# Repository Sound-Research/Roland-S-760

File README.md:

# Roland S-760

## Overview
Documentation for the Roland S-760 sampler.

## Specifications
- Type: Sampler
- Manufacturer: Roland

## Mouse

The S-760 uses a DB-9 mouse port with the **MSX mouse protocol** (nibble-clock based, originally MITSUMI).
The original Roland mouse is the MU-1, which is a rebranded MITSUMI MSX mouse.

**Important:** The MSX DB-9 pinout has **pin 5 = +5V** and **pin 9 = GND**, which is **reversed** compared to Atari/Amiga DB-9 (pin 7 = +5V, pin 8 = GND).
Atari, Amiga, and Commodore mice are **not compatible** — they use different protocols and reversed power pins.

### Compatible adapters

#### MSX PS/2 mouse interface (recommended)

- **Source**: [Gotek Retro](https://www.gotek-retro.eu/msx-ps2-mouse-interface/) or [Tindie (Denjhang)](https://www.tindie.com/products/denjhang/msx-ps2-mouse-converter/)
- **Description**: ATtiny2313-based PS/2 to MSX mouse protocol converter
- **Status**: Confirmed working with S-760
- **Note**: Pressing both mouse buttons simultaneously toggles between mouse and joystick emulation modes, so simultaneous two-button operations don't work
- **Requires**: A native PS/2 mouse, or a USB mouse with genuine PS/2 compatibility mode (not all passive USB-to-PS/2 adapters work)

#### USB-to-MSX mouse adapter

- **Source**: Occasionally available on eBay (search "USB to MSX Mouse Adapter Towns Roland")
- **Description**: Direct USB to MSX mouse protocol converter
- **Status**: Confirmed working with S-760 by users
- **Note**: Small-batch/hobbyist product, stock varies

#### Original MSX mice

Any genuine MSX mouse works (Roland MU-1, Philips MSX mouse, etc.).
Increasingly rare and expensive.

### DIY USB-to-MSX mouse adapter

Two open-source projects exist using a **Raspberry Pi Pico** (RP2040):

#### MsxUsbMouseConverter (recommended)

- **Source**: [Retro-Do-MSX/MsxUsbMouseConverter](https://github.com/Retro-Do-MSX/MsxUsbMouseConverter)
- **Description**: USB mouse to MSX mouse converter using RP2040
- **Hardware**: Raspberry Pi Pico + USB-A female connector + 2x 22-ohm resistors + DB9 cable
- **Advantage**: Operates exclusively in MSX mouse mode (no joystick toggle), so both buttons work simultaneously — unlike the PS/2 adapter above
- **Includes**: 3D-printable case files

#### unz-hid-pico

- **Source**: [hsshss/unz-hid-pico](https://github.com/hsshss/unz-hid-pico)
- **Description**: USB mouse/gamepad to FM TOWNS and MSX protocol converter
- **Hardware**: Raspberry Pi Pico + OTG adapter + DB9 cable + 3.3V-to-5V level shifter
- **Schematic**: [OSHWLab](https://oshwlab.com/hsshss/unz-hid-pico)

#### Why not other microcontrollers?

- **ESP32 (original)**: No native USB host — software USB host exists but is unreliable
- **ESP32-S2/S3**: Has USB host but no existing MSX mouse project — would need custom firmware from scratch
- **Arduino Duemilanove**: No USB host — requires a USB Host Shield (MAX3421E) add-on board
- **Raspberry Pi Zero 2 W**: Linux is not real-time enough for the MSX protocol timing (0.18 ms clock response), and GPIO is 3.3V (MSX expects 5V)

### mouSTer USB mouse adapter (not compatible)

- **Source**: [C64 OS Store](https://c64os.com/store/)
- **Status**: **Not compatible** — does not support MSX protocol (only Atari ST, Amiga, and C64 modes)
- **Note**: Previously recommended by Claude in error, purchased based on that recommendation, and confirmed not to work with the S-760. The mouSTer lacks MSX protocol support entirely.

## Video Output

The S-760 (with OP-760-1 expansion) has a digital RGB video output via an 8-pin DIN connector.

### OP-760-1 video signal specifications

- **Signal type**: TTL digital RGB (RGBS — 1 bit per channel, 8 colours max)
- **Resolution**: 640x200 (CGA-class)
- **Horizontal sync**: ~15.7 kHz
- **Vertical sync**: ~60 Hz
- **Sync type**: Separate H-Sync and V-Sync
- **Connector**: 8-pin DIN (EIAJ)

#### DIN-8 pinout

| Pin | Signal |
| --- | --- |
| 1 | +5V (do not connect to RGBtoHDMI) |
| 2 | GND |
| 3 | No connection |
| 4 | H-Sync |
| 5 | V-Sync |
| 6 | Red |
| 7 | Green |
| 8 | Blue |

**Note:** Some sources (e.g. S-550 manual) list a different pin assignment.
Verify against your hardware or use a known-good pre-made cable.

#### References

- [llamamusic.com DIY page](https://llamamusic.com/s50s550/DIY_page.html) — S-50/S-550/S-760 video output details and DIN-8 pinout
- [llamamusic.com RGB-25N cable DIY](https://llamamusic.com/s50s550/Roland_RGB-25N_Monitor_Cable_DIY.html) — cable wiring guide
- [Jim Atwood — S-760 with OP-760-1](https://jimatwood.wordpress.com/2012/02/01/roland-s-760-sampler-with-op-760-1-video-output-and-mu-1-mouse/) — working setup photos
- [s760.free.fr monitors page](http://s760.free.fr/monitor.htm) — compatible monitor list

### RGBtoHDMI

- **Source**: [hoglet67/RGBtoHDMI](https://github.com/hoglet67/RGBtoHDMI)
- **Description**: Converts retro computer RGB/YUV video signals to HDMI
- **Hardware**: Raspberry Pi Zero + custom hat with CPLD
- **License**: GPL-3.0

#### Profile selection

Use **6-12_BIT_RGB > IBM PC Compatible > CGA**.
The S-760's video output matches CGA timing and signal characteristics (TTL RGB, 15.7 kHz, 200 lines, separate H/V sync).

#### Fullscreen output

By default RGBtoHDMI may show the image in a small window with black borders.
To get fullscreen output, use the on-screen menu (active button on the hat):

1. Press **Menu** button on the RGBtoHDMI hat
2. Navigate to **Scaling** settings
3. Set scaling to **Fill** or **Integer** (integer gives pixel-perfect scaling without stretching)
4. Adjust **overscan** values if there are still black borders

You can also try different **Resolution** options in the menu — some HDMI displays respond better to specific output resolutions (e.g. 1080p vs 720p).

#### Raspberry Pi setup

The RGBtoHDMI runs bare-metal firmware on a Raspberry Pi Zero (no OS needed).

1. **Download** the latest release zip from [hoglet67/RGBtoHDMI releases](https://github.com/hoglet67/RGBtoHDMI/releases)
2. **Format** a micro SD card as FAT32
3. **Extract** the zip to the root of the SD card (files should be in the root directory, not in a subfolder)
4. **Safely eject** the SD card from the PC
5. **Insert** the SD card into the Pi Zero

- **Recommended Pi**: Raspberry Pi Zero (non-W) — the WiFi radio on the W models can cause visual artifacts
- **If using a Pi Zero W**: disable radios by adding `dtoverlay=disable-wifi` and `dtoverlay=disable-bt` to `config.txt` on the SD card
- **Avoid Pi Zero 2 W**: different GPIO timing causes compatibility issues
- **Upgrading**: wipe the SD card first, do not overwrite an existing install — old saved profiles are not guaranteed to be compatible

## SCSI Storage

The S-760 uses SCSI for external storage. A ZuluSCSI Pico Slim replaces physical SCSI drives with SD card-based disk images.

### ZuluSCSI Pico Slim

- **Source**: [SamplerZone](https://samplerzone.com/products/zuluscsi-pico-slim)
- **Description**: Ultra-compact SCSI SD card emulator with DB25 connector
- **Hardware**: Raspberry Pi Pico W in a mini plug-in case
- **Included**: Pre-configured 64GB SD card
- **Features**:
  - Supports up to 7 SCSI IDs (multiple drives simultaneously)
  - Plug-and-play via DB25 SCSI port
  - Standard SD card with disk image files
  - Compatible with Roland, Akai, Ensoniq, Emu, Kurzweil, Korg, Yamaha samplers

## Sound Loading

Chicken Systems Translator is used to convert and load sounds onto the ZuluSCSI disk images for use on the S-760.

### Chicken Systems Translator 7

- **Source**: [Chicken Systems](https://www.chickensys.com/products2/translator/index.html)
- **Description**: Professional sample library conversion software
- **Platforms**: Mac OS X, Windows
- **Features**:
  - Converts between 50+ sampler and DAW formats including Roland, Akai, Emu, Kontakt, EXS24, SFZ, GigaStudio
  - Translates wavedata, keymaps, and effects parameters
  - Built-in Instrument Player for auditioning sounds before conversion
  - Reference Manager for repairing broken sample links
  - AutoSampler for recording internal and external equipment

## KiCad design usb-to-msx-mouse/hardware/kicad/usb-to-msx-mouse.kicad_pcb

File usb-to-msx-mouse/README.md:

# USB-to-MSX mouse adapter for Roland S-760

Open-source hardware adapter that lets you use a standard USB mouse (like the Logitech Trackman Marble) with the Roland S-760 sampler.

The S-760 uses the MSX mouse protocol on a DB-9 joystick port.
Original Roland MU-1 mice are rare and expensive.
This adapter is a custom PCB with an RP2040 microcontroller that translates USB HID mouse reports into MSX nibble protocol in real time.

## Features

- **Plug and forget** — no drivers, no configuration
- **USB-A input** — works with any standard USB mouse (boot protocol)
- **DB-9 output** — connects to the S-760's mouse port via standard serial cable
- **Custom PCB** — RP2040 directly on board (not a Pico module), ~20×40mm
- **JLCPCB-ready** — full production files included (Gerbers, BOM, CPL)
- **Under $16 NZD per unit** (in batches of 5)

## How it works

```
USB Mouse → [USB-A] → RP2040 (TinyUSB host) → 74HCT245 → [DB-9] → S-760
              ↑                                    ↑
           USB HID                           3.3V → 5V
         boot protocol                     level shifting
```

1. The RP2040 runs TinyUSB in USB host mode, receiving HID boot-protocol mouse reports
1. Mouse X/Y deltas accumulate between read cycles, scaled from USB DPI to MSX ~200 DPI
1. When the S-760 toggles the strobe line (DB-9 pin 8), a GPIO interrupt handler serves 4 nibbles of position data
1. Button state is output continuously on DB-9 pins 6 and 7
1. A 74HCT245 level shifter converts all outputs from 3.3V to 5V MSX levels

## Project structure

```
usb-to-msx-mouse/
├── firmware/           Pico SDK C project (TinyUSB host + MSX protocol)
│   ├── CMakeLists.txt
│   ├── src/            main.c, hid_app.c, mouse.c, config.h
│   └── include/        tusb_config.h
├── hardware/
│   ├── kicad/          KiCad 8 schematic and PCB layout
│   ├── bom.csv         Bill of materials with JLCPCB part numbers
│   ├── gerbers/        Production Gerber files
│   └── jlcpcb/         JLCPCB assembly files (BOM + CPL)
├── case/               3D printable snap-fit enclosure (STEP + STL)
├── docs/
│   ├── pinout.md       GPIO to DB-9 pin mapping
│   └── build-guide.md  Order, flash, assemble, test
├── LICENSE             MIT
└── README.md
```

## Quick start

### Build firmware

```bash
export PICO_SDK_PATH=/path/to/pico-sdk
cd firmware
mkdir build && cd build
cmake ..
make -j$(nproc)
```

### Flash

1. Hold BOOTSEL button on the PCB
1. Connect USB-A to USB-A cable between computer and adapter
1. Release BOOTSEL — adapter appears as `RPI-RP2` drive
1. Copy `build/usb-to-msx-mouse.uf2` to the drive

### Connect

1. DB-9 cable from adapter to S-760 mouse port
1. Plug USB mouse into adapter's USB-A port
1. Green LED lights up when mouse is recognized
1. Power on S-760 — cursor should work

See [docs/build-guide.md](docs/build-guide.md) for full step-by-step instructions.

## Configuration

Edit `firmware/src/config.h` to adjust:

- **`MOUSE_DPI`** — match your mouse's native DPI (300 for Trackman Marble, 800 for typical optical)
- **`MOUSE_DATA_REVERSE`** — set to 1 if data lines are wired in reverse order
- **Pin assignments** — if modifying the PCB layout

## Hardware specifications

- **MCU**: RP2040 (QFN-56, dual-core Cortex-M0+, 133 MHz)
- **Flash**: W25Q16JVSNIQ (2MB QSPI)
- **Level shifter**: 74HCT245 (SOIC-20)
- **Power**: 5V from MSX DB-9 pin 5 (USB-C fallback pads on PCB)
- **Board size**: ~20×40mm, 2-layer
- **Connectors**: USB-A female (TH), DB-9 male (TH) — hand-soldered

## Cost breakdown (5 units)

| Item | Cost (NZD) |
| --- | --- |
| PCB fabrication (5x) | $4 |
| SMT assembly + components | $40 |
| 3D printed cases (5x) | $15 |
| Shipping to NZ | $12 |
| Through-hole connectors | $8 |
| **Total (5 units)** | **~$79** |
| **Per unit** | **~$16** |

## Credits

Firmware based on [unz-hid-pico](https://github.com/hsshss/unz-hid-pico) by hsshss (MIT license).

## References

- [MSX Mouse/Trackball protocol](https://www.msx.org/wiki/Mouse/Trackball)
- [RP2040 hardware design guide](https://datasheets.raspberrypi.com/rp2040/hardware-design-with-rp2040.pdf)
- [TinyUSB documentation](https://docs.tinyusb.org/)

## License

[MIT](LICENSE)

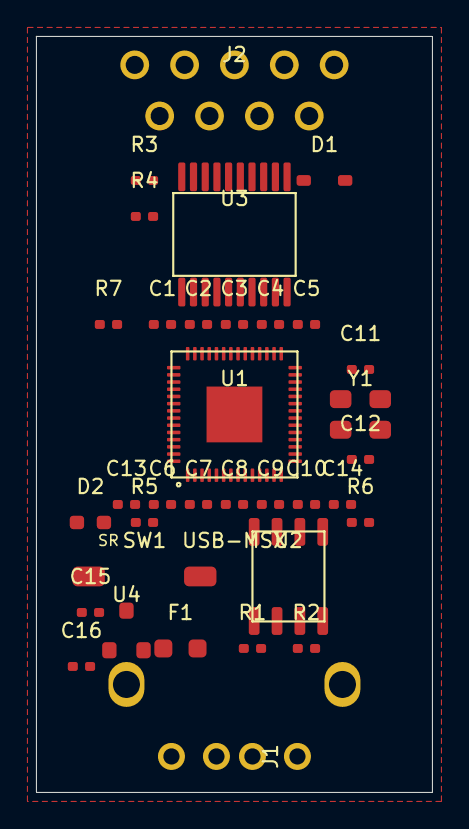
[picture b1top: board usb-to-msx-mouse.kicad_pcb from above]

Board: 2 copper layers, 22.0 x 42.0 mm, 34 parts (0 on the bottom side), 35 nets, no tracks yet.

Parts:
C1, C2, C3, C4, C5, C6, C7, C8, C9, C10: 100nF; R_0402_1005Metric
C11, C12: 27pF; R_0402_1005Metric
C13, C14, C15, C16: 1uF; R_0402_1005Metric
D1: BAT54; D_SOD-323
D2: Green; LED_0603_1608Metric
F1: 500mA; Fuse_0805_2012Metric
J1: USB_A; USB_A_Molex_67643_Horizontal
J2: DB9_Male; DSUB-9_Male_Horizontal_P2.77x2.84mm_EdgePinOffset7.70mm
R1, R2: 27R; R_0402_1005Metric
R3: 2.2k; R_0402_1005Metric
R4: 3.3k; R_0402_1005Metric
R5: 1k; R_0402_1005Metric
R6, R7: 10k; R_0402_1005Metric
SW1: BOOTSEL; SW_SPST_TL3342
U1: RP2040; QFN-56-1EP_7x7mm_P0.4mm
U2: W25Q16; SOIC-8_3.9x4.9mm_P1.27mm
U3: 74HCT245; TSSOP-20_4.4x6.5mm_P0.65mm
U4: XC6206; SOT-23
Y1: 12MHz; Crystal_SMD_3225-4Pin_3.2x2.5mm

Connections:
5V_MSX: D1.2, J2.5
+3V3: C1.1, C2.1, C3.1, C4.1, C5.1, C6.1, C7.1, C8.1, C9.1, C10.1, C14.1, C16.1, R6.2, R7.2, U1.1, U1.10, U1.17, U1.23, U1.34, U1.43, U1.44, U1.45, U1.49, U1.50, U2.8, U4.2
+5V: C15.1, D1.1, F1.1, U3.20, U4.3
DB9_D0: J2.1, U3.18
DB9_D1: J2.2, U3.17
DB9_D2: J2.3, U3.16
DB9_D3: J2.4, U3.15
DB9_LBTN: J2.6, U3.14
DB9_RBTN: J2.7, U3.13
DVDD: C13.1, U1.24, U1.46
GND: C1.2, C2.2, C3.2, C4.2, C5.2, C6.2, C7.2, C8.2, C9.2, C10.2, C11.2, C12.2, C13.2, C14.2, C15.2, C16.2, D2.2, J1.4, J1.5, J2.9, R4.2, SW1.2, U1.20, U1.57, U2.4, U3.1, U3.8, U3.9, U3.10, U3.19, U4.1, Y1.2, Y1.4
GPIO2: U1.4, U3.2
GPIO3: U1.5, U3.3
GPIO4: U1.6, U3.4
GPIO5: U1.7, U3.5
GPIO6: U1.8, U3.6
GPIO7: U1.9, U3.7
GPIO8: R3.2, R4.1, U1.11
GPIO25: R5.1, U1.38
LED_A: D2.1, R5.2
QSPI_SCLK: U1.52, U2.6
QSPI_SD0: U1.53, U2.5
QSPI_SD1: U1.55, U2.2
QSPI_SD2: U1.54, U2.3
QSPI_SD3: U1.51, U2.7
QSPI_SS: R6.1, SW1.1, U1.56, U2.1
RUN: R7.1, U1.27
STROBE_5V: J2.8, R3.1
USB_DM: R1.2, U1.47
USB_DM_R: J1.2, R1.1
USB_DP: R2.2, U1.48
USB_DP_R: J1.3, R2.1
VBUS_FUSED: F1.2, J1.1
XIN: C11.1, U1.21, Y1.1
XOUT: C12.1, U1.22, Y1.3

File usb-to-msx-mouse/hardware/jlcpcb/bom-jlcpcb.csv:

Comment,Designator,Footprint,LCSC Part #
RP2040 Microcontroller,U1,QFN-56-1EP_7x7mm_P0.4mm,C2040
W25Q16JVSNIQ 2MB QSPI Flash,U2,SOIC-8_3.9x4.9mm_P1.27mm,C131024
74HCT245 Level Shifter,U3,TSSOP-20_4.4x6.5mm_P0.65mm,C6636
XC6206P332MR 3.3V LDO,U4,SOT-23,C5446
12MHz Crystal,Y1,Crystal_SMD_3225-4Pin_3.2x2.5mm,C9002
100nF Decoupling Cap,C1 C2 C3 C4 C5 C6 C7 C8 C9 C10,C_0402_1005Metric,C307331
27pF Crystal Load Cap,C11 C12,C_0402_1005Metric,C1557
1uF Cap,C13 C14 C15 C16,C_0402_1005Metric,C52923
27R USB Series Resistor,R1 R2,R_0402_1005Metric,C25105
2.2k Strobe Divider Top,R3,R_0402_1005Metric,C25879
3.3k Strobe Divider Bottom,R4,R_0402_1005Metric,C25890
1k LED Resistor,R5,R_0402_1005Metric,C11702
10k Pull-up,R6 R7,R_0402_1005Metric,C25744
Green Status LED,D2,LED_0603_1608Metric,C72043
BAT54 Schottky Diode,D1,D_SOD-323,C89228
500mA Polyfuse,F1,Fuse_0805_2012Metric,C369159
BOOTSEL Tactile Switch,SW1,SW_SPST_TL3342,C318884

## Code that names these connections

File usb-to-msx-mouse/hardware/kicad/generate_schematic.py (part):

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        # GPIO pins on left side
        ("2", "GPIO0", -16.51, 22.86, "R"),
        ("3", "GPIO1", -16.51, 20.32, "R"),
        ("4", "GPIO2", -16.51, 17.78, "R"),
        ("5", "GPIO3", -16.51, 15.24, "R"),
        ("6", "GPIO4", -16.51, 12.7, "R"),
        ("7", "GPIO5", -16.51, 10.16, "R"),
        ("8", "GPIO6", -16.51, 7.62, "R"),
        ("9", "GPIO7", -16.51, 5.08, "R"),
        ("11", "GPIO8", -16.51, 2.54, "R"),
        ("12", "GPIO9", -16.51, 0, "R"),
        ("13", "GPIO10", -16.51, -2.54, "R"),
        ("14", "GPIO11", -16.51, -5.08, "R"),
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        ("35", "GPIO22", 16.51, 7.62, "L"),
        ("36", "GPIO23", 16.51, 5.08, "L"),
        ("37", "GPIO24", 16.51, 2.54, "L"),
        ("38", "GPIO25", 16.51, 0, "L"),
        ("39", "GPIO26/ADC0", 16.51, -2.54, "L"),
        ("40", "GPIO27/ADC1", 16.51, -5.08, "L"),
        ("41", "GPIO28/ADC2", 16.51, -7.62, "L"),
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    elements.append(component("W25Q16JVSNIQ", "U2", "W25Q16JVSNIQ", fl_x, fl_y))

    # Flash connections to RP2040 QSPI pins
    # RP2040 QSPI_SCLK (pin 52) at rp_x-7.62, rp_y+21.59 → Flash CLK (pin 6) at fl_x-10.16, fl_y-1.27
    elements.append(label("QSPI_SCLK", rp_x - 7.62, rp_y + 21.59, 270))
    elements.append(label("QSPI_SCLK", fl_x - 13, fl_y - 1.27, 0))
    # QSPI_SD0
    elements.append(label("QSPI_SD0", rp_x - 5.08, rp_y + 21.59, 270))
    elements.append(label("QSPI_SD0", fl_x - 13, fl_y + 1.27, 0))
    # QSPI_SD1
    elements.append(label("QSPI_SD1", rp_x - 2.54, rp_y + 21.59, 270))
    elements.append(label("QSPI_SD1", fl_x + 13, fl_y + 3.81, 180))
    # QSPI_SD2
    elements.append(label("QSPI_SD2", rp_x, rp_y + 21.59, 270))
    elements.append(label("QSPI_SD2", fl_x + 13, fl_y + 1.27, 180))
    # QSPI_SD3
    elements.append(label("QSPI_SD3", rp_x + 2.54, rp_y + 21.59, 270))
    elements.append(label("QSPI_SD3", fl_x + 13, fl_y - 1.27, 180))
    # QSPI_SS → Flash ~CS
    elements.append(label("QSPI_SS", rp_x + 5.08, rp_y + 21.59, 270))
    elements.append(label("QSPI_SS", fl_x - 13, fl_y + 3.81, 0))

    # Flash power
    elements.append(power_sym("+3V3", fl_x, fl_y - 8.89, 180))
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
    # Flash CS pull-up resistor (10kΩ)
    elements.append(component("R", "R6", "10k", fl_x - 18, fl_y - 5))
    elements.append(label("QSPI_SS", fl_x - 18, fl_y - 5 + 3.81, 90))
    elements.append(power_sym("+3V3", fl_x - 18, fl_y - 5 - 3.81, 180))

    # === Section: 12MHz Crystal (below-right of RP2040) ===
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    elements.append(component("Crystal_4Pin", "Y1", "12MHz", cr_x, cr_y))

    # Crystal connections to XIN/XOUT
    elements.append(label("XIN", rp_x + 7.62, rp_y + 21.59, 270))
    elements.append(label("XIN", cr_x - 5, cr_y, 0))
    elements.append(label("XOUT", rp_x + 10.16, rp_y + 21.59, 270))
    elements.append(label("XOUT", cr_x + 5, cr_y, 180))

    # Crystal load caps (27pF each)
    elements.append(component("C", "C11", "27pF", cr_x - 5, cr_y + 8))
    elements.append(label("XIN", cr_x - 5, cr_y + 8 - 3.81, 90))
    elements.append(power_sym("GND", cr_x - 5, cr_y + 8 + 3.81))

    elements.append(component("C", "C12", "27pF", cr_x + 5, cr_y + 8))
    elements.append(label("XOUT", cr_x + 5, cr_y + 8 - 3.81, 90))
    elements.append(power_sym("GND", cr_x + 5, cr_y + 8 + 3.81))

    # Crystal GND pins
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    elements.append(power_sym("+3V3", rp_x + 10.16, rp_y - 29.21, 180))

    # DVDD — internal 1.1V core (needs 1µF decoupling, connected to VREG_VOUT)
    elements.append(label("DVDD", rp_x - 12.7, rp_y + 26.67, 270))

    # VREG_VIN — connect to 3.3V
    elements.append(power_sym("+3V3", rp_x - 7.62, rp_y + 30, 180))
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
    # VREG_VOUT — 1.1V core, connect to DVDD with decoupling cap
    elements.append(label("VREG_VOUT", rp_x - 2.54, rp_y + 26.67, 270))
    elements.append(label("DVDD", rp_x - 2.54, rp_y + 30, 270))
    # Connect VREG_VOUT to DVDD
    elements.append(component("C", "C13", "1uF", rp_x - 8, rp_y + 33))
    elements.append(label("DVDD", rp_x - 8, rp_y + 33 - 3.81, 90))
    elements.append(power_sym("GND", rp_x - 8, rp_y + 33 + 3.81))

    # TESTEN — tie to GND
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    # === Section: BOOTSEL Button (connected to QSPI_SS) ===
    bs_x, bs_y = 100, 155
    elements.append(component("SW_Push", "SW1", "BOOTSEL", bs_x, bs_y))
    elements.append(label("QSPI_SS", bs_x - 7, bs_y, 0))
    elements.append(power_sym("GND", bs_x + 7, bs_y))

    # === Section: USB-A Host Port (left side) ===
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
    # USB D- with 27Ω series resistor
    elements.append(component("R", "R1", "27R", usb_x + 25, usb_y - 2))
    elements.append(label("USB_DM", usb_x + 25, usb_y - 2 - 3.81, 90))
    elements.append(wire(usb_x + 7.62, usb_y + 2.54, usb_x + 25, usb_y + 2.54))
    elements.append(wire(usb_x + 25, usb_y + 2.54, usb_x + 25, usb_y - 2 + 3.81))

    # USB D+ with 27Ω series resistor
    elements.append(component("R", "R2", "27R", usb_x + 32, usb_y - 2))
    elements.append(label("USB_DP", usb_x + 32, usb_y - 2 - 3.81, 90))
    elements.append(wire(usb_x + 7.62, usb_y, usb_x + 32, usb_y))
    elements.append(wire(usb_x + 32, usb_y, usb_x + 32, usb_y - 2 + 3.81))

    # USB D+/D- labels to RP2040
    elements.append(label("USB_DM", rp_x - 12.7, rp_y + 21.59, 270))
    elements.append(label("USB_DP", rp_x - 10.16, rp_y + 21.59, 270))

    # USB GND
    elements.append(power_sym("GND", usb_x + 7.62 + 3, usb_y + 2.54 + 5))
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
    # A-side inputs from RP2040 GPIOs (active-low driven by firmware)
    gpio_labels = [
        ("GPIO2", "A1", -10.16),   # Data 0
        ("GPIO3", "A2", -7.62),    # Data 1
        ("GPIO4", "A3", -5.08),    # Data 2
        ("GPIO5", "A4", -2.54),    # Data 3
        ("GPIO6", "A5", 0),        # Left btn
        ("GPIO7", "A6", 2.54),     # Right btn
    ]
    for gpio_name, a_pin, y_off in gpio_labels:
        elements.append(label(gpio_name, ls_x - 15, ls_y - y_off, 0))
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
    # RP2040 GPIO labels (left side of RP2040)
    rp_gpios = [
        ("GPIO2", 17.78),
        ("GPIO3", 15.24),
        ("GPIO4", 12.7),
        ("GPIO5", 10.16),
        ("GPIO6", 7.62),
        ("GPIO7", 5.08),
    ]
    for gpio_name, y_off in rp_gpios:
        elements.append(label(gpio_name, rp_x - 19, rp_y - y_off, 0))
        elements.append(wire(rp_x - 19, rp_y - y_off, rp_x - 16.51, rp_y - y_off))

    # GPIO8 label for strobe
    elements.append(label("GPIO8", rp_x - 19, rp_y - 2.54, 0))
    elements.append(wire(rp_x - 19, rp_y - 2.54, rp_x - 16.51, rp_y - 2.54))

    # GPIO25 for LED
    elements.append(label("GPIO25", rp_x + 19, rp_y, 180))
    elements.append(wire(rp_x + 16.51, rp_y, rp_x + 19, rp_y))

    # Unused A7, A8 — tie to GND
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    elements.append(wire(db_x - 15, db_y + 3.81, db_x + 7.62, db_y + 3.81))
    elements.append(text_note("Right btn", db_x + 12, db_y + 3.81, 1.0))

    # DB-9 pin 8 (Strobe) — voltage divider to GPIO8
    # R3 (2.2kΩ) from pin 8, R4 (3.3kΩ) to GND, junction to GPIO8
    div_x, div_y = db_x + 25, db_y + 15
    elements.append(component("R", "R3", "2.2k", div_x, div_y - 5))
    elements.append(component("R", "R4", "3.3k", div_x, div_y + 5))
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    elements.append(wire(div_x, db_y + 6.35, div_x, div_y - 5 - 3.81))
    elements.append(wire(div_x, div_y - 5 + 3.81, div_x, div_y + 5 - 3.81))
    elements.append(power_sym("GND", div_x, div_y + 5 + 3.81))
    elements.append(label("GPIO8", div_x + 5, div_y, 180))
    elements.append(wire(div_x, div_y, div_x + 5, div_y))
    elements.append(junction(div_x, div_y))
    elements.append(text_note("Strobe (5V→3V divider)", db_x + 12, db_y + 6.35, 1.0))
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    led_x, led_y = 175, 95
    elements.append(component("LED", "D2", "Green", led_x, led_y))
    elements.append(component("R", "R5", "1k", led_x, led_y - 10))
    elements.append(label("GPIO25", led_x, led_y - 10 - 3.81, 90))
    elements.append(power_sym("GND", led_x, led_y + 3.81))
    elements.append(wire(led_x, led_y - 3.81, led_x, led_y - 10 + 3.81))

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        (rp_x + 16.51, rp_y - 7.62),    # GPIO22
        (rp_x + 16.51, rp_y - 5.08),    # GPIO23
        (rp_x + 16.51, rp_y - 2.54),    # GPIO24
        # GPIO25 is used for LED
        (rp_x + 16.51, rp_y + 2.54),    # GPIO26
        (rp_x + 16.51, rp_y + 5.08),    # GPIO27
        (rp_x + 16.51, rp_y + 7.62),    # GPIO28
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
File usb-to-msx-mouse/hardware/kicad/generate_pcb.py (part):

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    3: "+3V3",
    4: "USB_DP",
    5: "USB_DM",
    6: "GPIO2",
    7: "GPIO3",
    8: "GPIO4",
    9: "GPIO5",
    10: "GPIO6",
    11: "GPIO7",
    12: "GPIO8",
    13: "GPIO25",
    14: "QSPI_SCLK",
    15: "QSPI_SD0",
    16: "QSPI_SD1",
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    24: "USB_DM_R",    # Between USB connector and series resistor
    25: "USB_DP_R",    # Between USB connector and series resistor
    26: "VBUS_FUSED",  # Between polyfuse and USB-A VBUS
    27: "STROBE_5V",   # DB-9 pin 8 before voltage divider
    28: "STROBE_DIV",  # Midpoint of voltage divider (= GPIO8)
    29: "DB9_D0",      # 74HCT245 B1 → DB-9 pin 1
    30: "DB9_D1",      # 74HCT245 B2 → DB-9 pin 2
    31: "DB9_D2",      # 74HCT245 B3 → DB-9 pin 3
    32: "DB9_D3",      # 74HCT245 B4 → DB-9 pin 4
    33: "DB9_LBTN",    # 74HCT245 B5 → DB-9 pin 6
    34: "DB9_RBTN",    # 74HCT245 B6 → DB-9 pin 7
    35: "5V_MSX",      # DB-9 pin 5 before diode
    36: "LED_A",       # Between LED resistor and LED anode
}
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

def fp_crystal_3225(ref, value, x, y, nets, angle=0):
    """3225 crystal: pin 1=XIN, pin 2=GND, pin 3=XOUT, pin 4=GND."""
    lines = [fp_header("Crystal:Crystal_SMD_3225-4Pin_3.2x2.5mm", ref, value, x, y, angle)]
    lines.append(pad_smd("1", -1.1, -0.85, 1.2, 1.0, nets[1], angle))
    lines.append(pad_smd("2", 1.1, -0.85, 1.2, 1.0, nets[2], angle))
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    ls_y = OY + 11
    ls_nets = {
        1: 1,    # DIR → GND (A→B)
        2: 6,    # A1 ← GPIO2
        3: 7,    # A2 ← GPIO3
        4: 8,    # A3 ← GPIO4
        5: 9,    # A4 ← GPIO5
        6: 10,   # A5 ← GPIO6
        7: 11,   # A6 ← GPIO7
        8: 1,    # A7 → GND (unused)
        9: 1,    # A8 → GND (unused)
        10: 1,   # GND
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        1: 3, 10: 3, 17: 3, 23: 3, 34: 3, 43: 3, 50: 3,
        # GPIO pins used
        2: 0, 3: 0,           # GPIO0, GPIO1 — unused
        4: 6,                  # GPIO2 → data 0
        5: 7,                  # GPIO3 → data 1
        6: 8,                  # GPIO4 → data 2
        7: 9,                  # GPIO5 → data 3
        8: 10,                 # GPIO6 → left btn
        9: 11,                 # GPIO7 → right btn
        11: 12,                # GPIO8 → strobe input (via divider)
        # Unused GPIOs
        12: 0, 13: 0, 14: 0, 15: 0, 16: 0,  # GPIO9-13
        18: 0, 19: 0,         # GPIO14-15
        28: 0, 29: 0, 30: 0, 31: 0, 32: 0, 33: 0,  # GPIO16-21
        35: 0, 36: 0, 37: 0,  # GPIO22-24
        38: 13,                # GPIO25 → LED
        39: 0, 40: 0, 41: 0, 42: 0,  # GPIO26-29
        # Special pins
        20: 1,                 # TESTEN → GND
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    footprints.append(fp_qfn56("U1", "RP2040", rp_x, rp_y, rp_nets))

    # ─── 12MHz Crystal (Y1) — right of RP2040, near XIN/XOUT ────────────
    # XIN = pin 21 at (rp_x+3.375, rp_y+0.2), XOUT = pin 22 at (rp_x+3.375, rp_y-0.2).
    # Crystal 3225: pads span ±1.7mm in X, ±1.35mm in Y from center.
    # At (cx+7, rp_y): inner pads at cx+5.3, RP2040 right pads at cx+3.75. Gap=1.55mm ✓
    # Outer pads at cx+8.7, board right edge cx+10. Margin=1.3mm ✓
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
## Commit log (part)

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2026-02-09 added kb article, added .iso to git ignore
2026-03-02 Fix mouse documentation: S-760 uses MSX protocol, not Atari/Amiga
    The mouSTer adapter was previously documented as the mouse solution but
    does not support the MSX mouse protocol the S-760 requires. Added correct
    compatible adapters (MSX PS/2 interface, USB-to-MSX) and documented the
    reversed power pinout (pin 5 = +5V, pin 9 = GND vs Atari/Amiga standard).
2026-03-02 Document RGBtoHDMI Pi Zero SD card setup instructions
    Add firmware download source, flashing steps, and Pi Zero
    compatibility notes to the RGBtoHDMI section.
2026-03-02 Add video output specs, RGBtoHDMI profile guide, and DIY mouse adapter research
    - Document OP-760-1 signal specs (CGA-class TTL RGB, DIN-8 pinout)
    - Add reference links for video output wiring and compatible monitors
    - Document CGA profile selection and fullscreen scaling settings
    - Add two open-source Raspberry Pi Pico USB-to-MSX mouse projects
    - Document why ESP32/Arduino/Pi Zero 2 W are not suitable for DIY adapter
2026-03-05 Add USB-to-MSX mouse adapter project (firmware, hardware, case)
    Complete open-source hardware project for USB mouse to MSX protocol
    adapter, designed for the Roland S-760 sampler.
    Firmware: RP2040 TinyUSB host + MSX nibble protocol (based on unz-hid-pico)
    Hardware: KiCad 9 schematic + PCB (22x52mm, 2-layer, JLCPCB-ready)
    - RP2040 QFN-56 with QSPI flash, 12MHz crystal
    - 74HCT245 level shifter (3.3V→5V)
